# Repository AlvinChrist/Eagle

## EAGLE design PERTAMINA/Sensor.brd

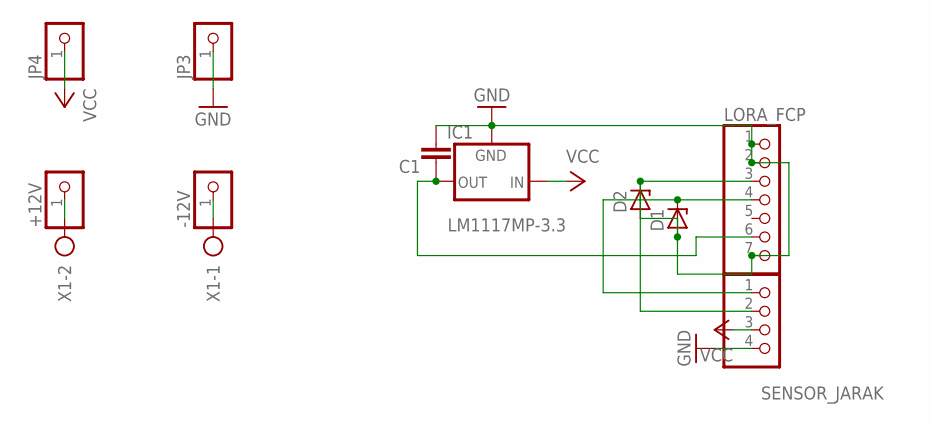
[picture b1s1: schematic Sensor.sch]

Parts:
+12V: PINHD-1X1; 1X01
-12V: PINHD-1X1; 1X01
C1: C-EU025-024X044; C025-024X044
D1, D2: ZENER-DIODEDO35Z10; DO35Z10
IC1: LM1117MP-3.3; SOT223
JP3, JP4: PINHD-1X1; 1X01
LORA_FCP: PINHD-1X7; 1X07
SENSOR_JARAK: PINHD-1X4; 1X04
X1: AK300/2

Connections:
3.3: C1.2, IC1.2 (OUT), IC1.4 (OUT), LORA_FCP.6
GND: C1.1, D1.A, D2.A, IC1.1 (GND), JP3.1, LORA_FCP.1, LORA_FCP.2, LORA_FCP.7, SENSOR_JARAK.4
GND12: -12V.1, X1.1
unnamed: +12V.1, X1.2
RX: D2.C, LORA_FCP.3, SENSOR_JARAK.2
TX: D1.C, LORA_FCP.4, SENSOR_JARAK.1
VCC: IC1.3 (IN), JP4.1, SENSOR_JARAK.3

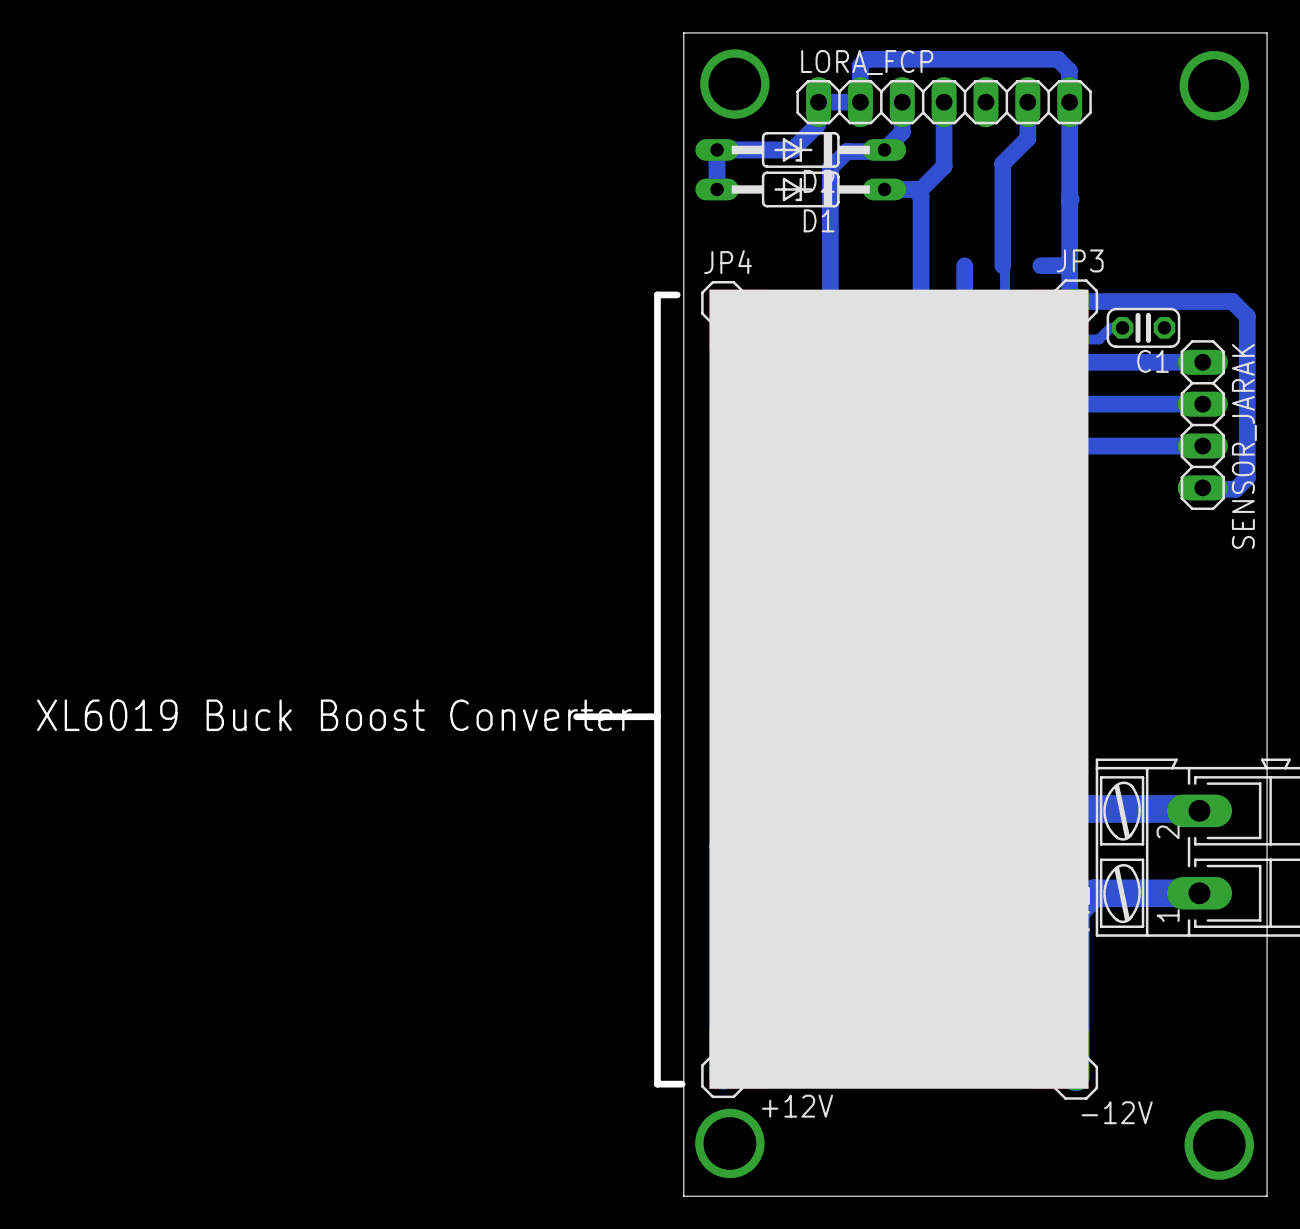
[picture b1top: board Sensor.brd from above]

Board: 2 copper layers, 35.4 x 70.6 mm, 11 parts (1 on the bottom side), 7 nets.

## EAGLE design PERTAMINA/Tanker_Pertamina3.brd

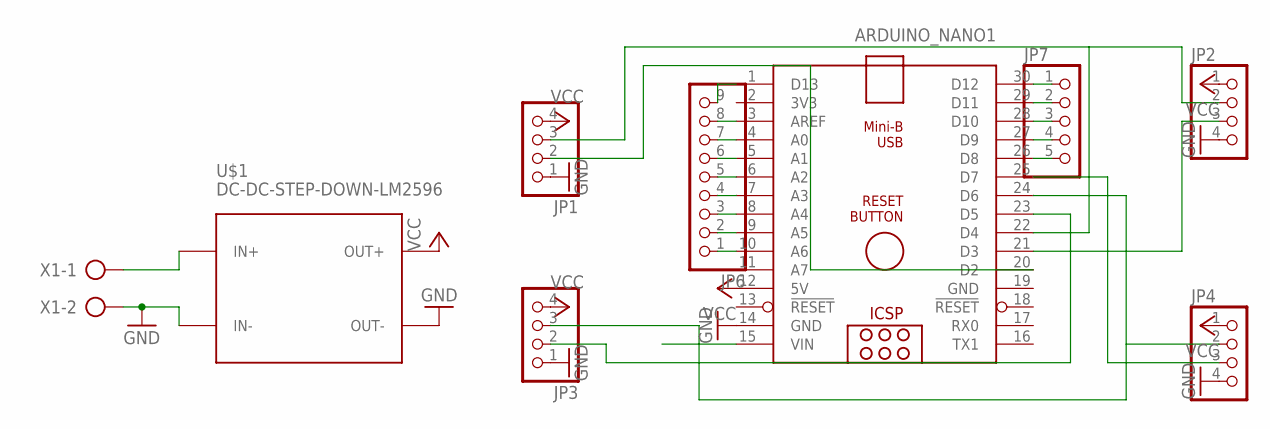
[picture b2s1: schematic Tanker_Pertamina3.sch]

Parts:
ARDUINO_NANO1: ARDUINO_NANO
JP1, JP2, JP3, JP4: PINHD-1X4; 1X04
JP6: PINHD-1X9; 1X09
JP7: PINHD-1X5; 1X05
U$1: DC-DC-STEP-DOWN-LM2596
X1: AK300/2

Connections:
7-12V: ARDUINO_NANO1.15 (VIN)
GND: ARDUINO_NANO1.14 (GND), ARDUINO_NANO1.19 (GND), JP1.1, JP2.4, JP3.1, JP4.4, U$1.IN-, U$1.OUT-, X1.2
unnamed: ARDUINO_NANO1.20 (D2), JP1.2
unnamed: ARDUINO_NANO1.10 (A6), JP6.1
unnamed: ARDUINO_NANO1.21 (D3), JP2.3
unnamed: ARDUINO_NANO1.23 (D5), JP3.2
unnamed: ARDUINO_NANO1.25 (D7), JP4.3
unnamed: ARDUINO_NANO1.9 (A5), JP6.2
unnamed: ARDUINO_NANO1.8 (A4), JP6.3
unnamed: ARDUINO_NANO1.7 (A3), JP6.4
unnamed: ARDUINO_NANO1.6 (A2), JP6.5
unnamed: ARDUINO_NANO1.5 (A1), JP6.6
unnamed: ARDUINO_NANO1.4 (A0), JP6.7
unnamed: ARDUINO_NANO1.3 (AREF), JP6.8
unnamed: ARDUINO_NANO1.1 (D13), JP6.9
unnamed: ARDUINO_NANO1.30 (D12), JP7.1
unnamed: ARDUINO_NANO1.29 (D11), JP7.2
unnamed: ARDUINO_NANO1.28 (D10), JP7.3
unnamed: ARDUINO_NANO1.27 (D9), JP7.4
unnamed: ARDUINO_NANO1.26 (D8), JP7.5
unnamed: U$1.IN+, X1.1
TRIGGER_BELAKANG: ARDUINO_NANO1.24 (D6), JP3.3, JP4.2
TRIG_DEPAN: ARDUINO_NANO1.22 (D4), JP1.3, JP2.2
VCC: ARDUINO_NANO1.12 (5V), JP1.4, JP2.1, JP3.4, JP4.1, U$1.OUT+

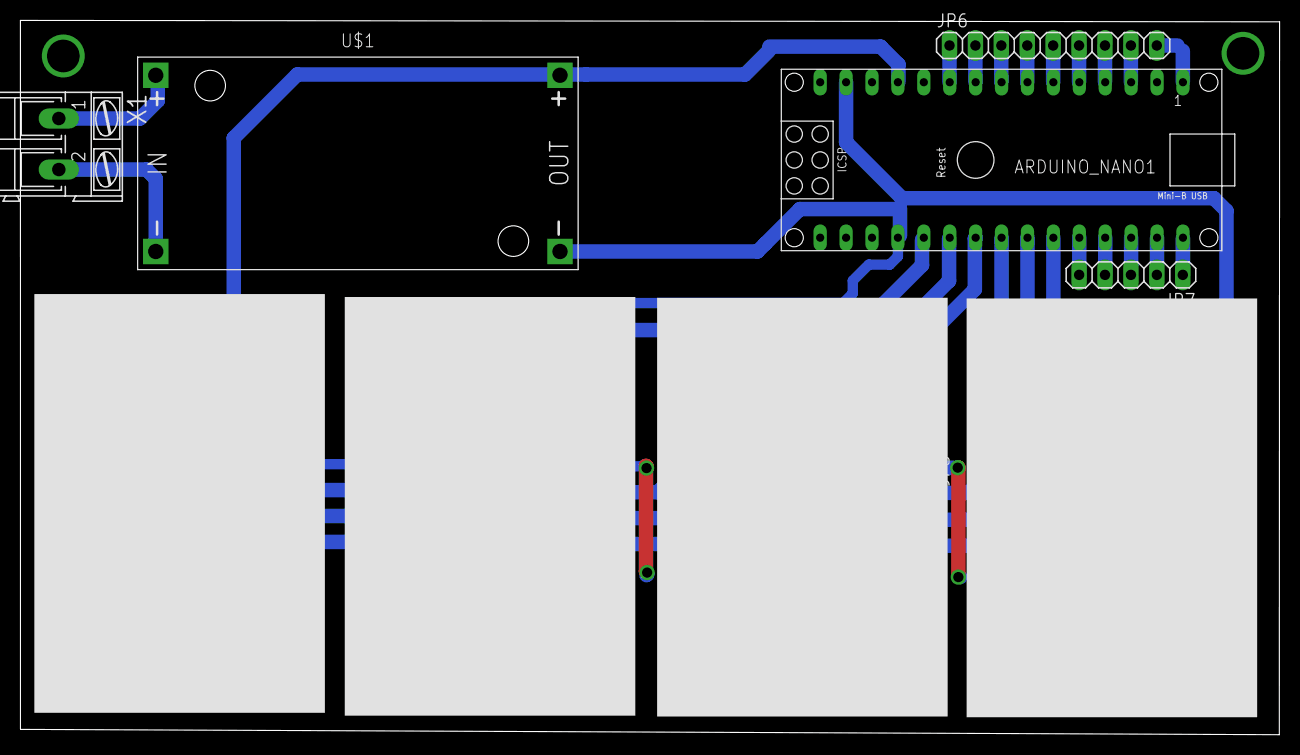
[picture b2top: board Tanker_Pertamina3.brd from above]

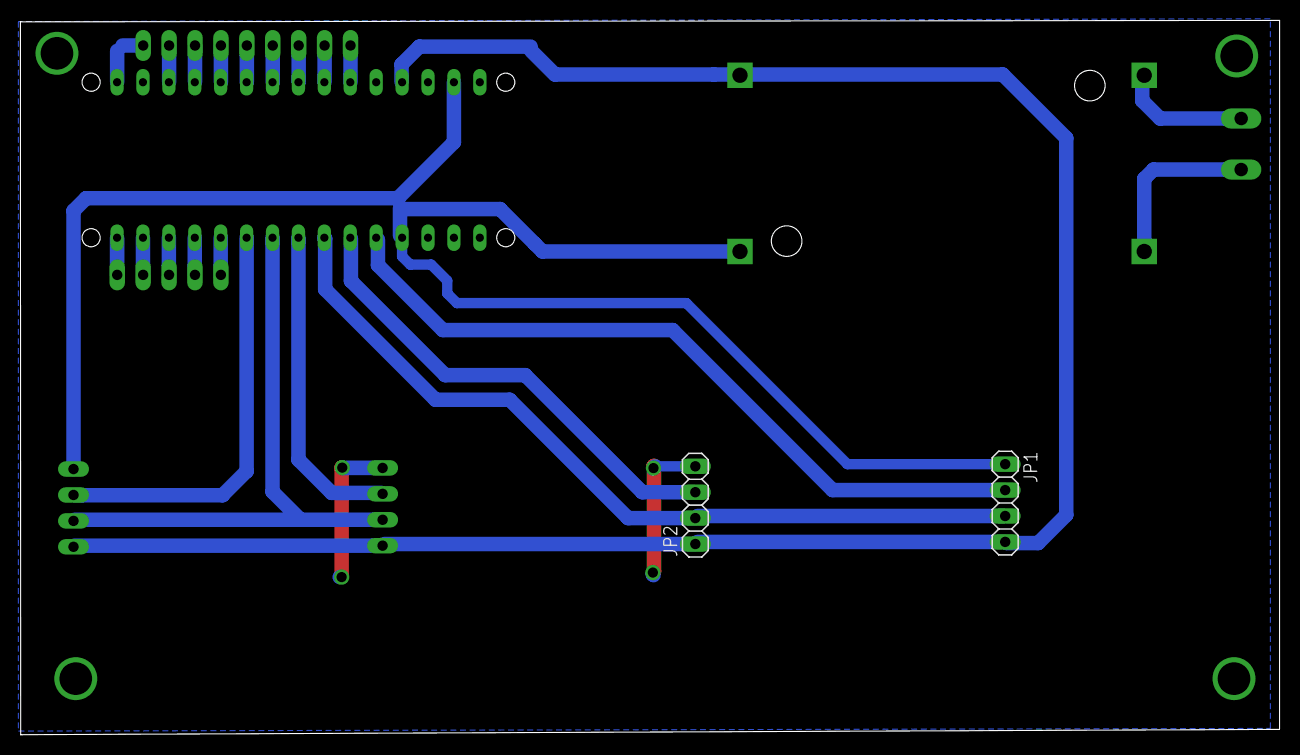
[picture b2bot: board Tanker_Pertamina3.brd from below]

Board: 2 copper layers, 123.4 x 70.0 mm, 9 parts (2 on the bottom side), 23 nets.

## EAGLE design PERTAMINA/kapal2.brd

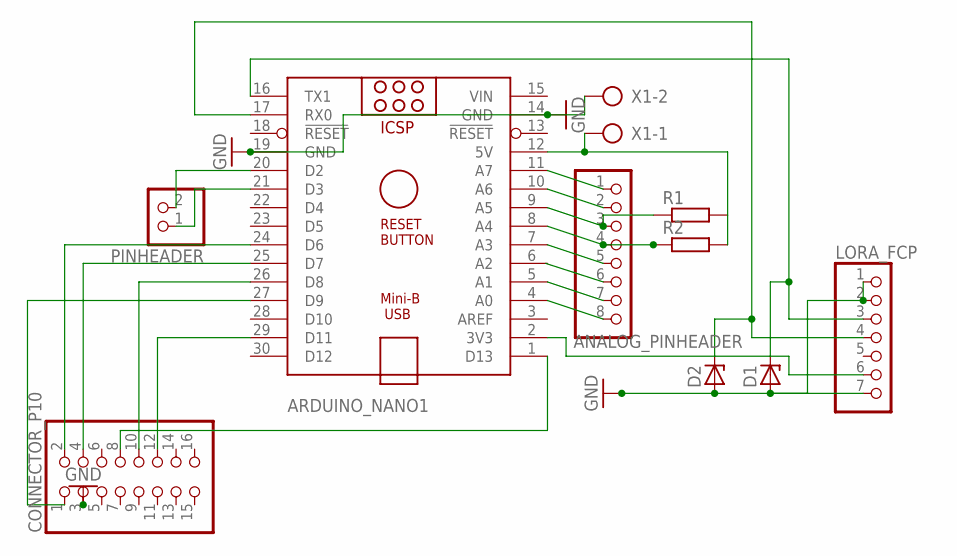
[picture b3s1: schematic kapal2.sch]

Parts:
ANALOG_PINHEADER: PINHD-1X8; 1X08
ARDUINO_NANO1: ARDUINO_NANO
CONNECTOR_P10: PINHD-2X8; 2X08
D1, D2: ZENER-DIODEDO35Z10; DO35Z10
LORA_FCP: PINHD-1X7; 1X07
PINHEADER: PINHD-1X2; 1X02
R1, R2: R-EU_0204/7; 0204/7
X1: AK300/2

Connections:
D7: ARDUINO_NANO1.25 (D7), CONNECTOR_P10.4
D13: ARDUINO_NANO1.1 (D13), CONNECTOR_P10.8
GND: ARDUINO_NANO1.14 (GND), ARDUINO_NANO1.19 (GND), CONNECTOR_P10.3, D1.A, D2.A, LORA_FCP.1, LORA_FCP.2, LORA_FCP.7, X1.2
unnamed: ARDUINO_NANO1.27 (D9), CONNECTOR_P10.1
unnamed: ARDUINO_NANO1.16 (TX1), D1.C, LORA_FCP.3
unnamed: ARDUINO_NANO1.24 (D6), CONNECTOR_P10.2
unnamed: ARDUINO_NANO1.26 (D8), CONNECTOR_P10.10
unnamed: ARDUINO_NANO1.29 (D11), CONNECTOR_P10.12
unnamed: ANALOG_PINHEADER.3, ARDUINO_NANO1.9 (A5), R1.1
unnamed: ARDUINO_NANO1.12 (5V), R1.2, R2.2, X1.1
unnamed: ARDUINO_NANO1.17 (RX0), D2.C, LORA_FCP.4
unnamed: ARDUINO_NANO1.20 (D2), PINHEADER.2
unnamed: ARDUINO_NANO1.2 (3V3), LORA_FCP.6
unnamed: ARDUINO_NANO1.21 (D3), PINHEADER.1
unnamed: ANALOG_PINHEADER.1, ARDUINO_NANO1.11 (A7)
unnamed: ANALOG_PINHEADER.2, ARDUINO_NANO1.10 (A6)
unnamed: ANALOG_PINHEADER.4, ARDUINO_NANO1.8 (A4), R2.1
unnamed: ANALOG_PINHEADER.5, ARDUINO_NANO1.7 (A3)
unnamed: ANALOG_PINHEADER.7, ARDUINO_NANO1.5 (A1)
unnamed: ANALOG_PINHEADER.8, ARDUINO_NANO1.4 (A0)
VIN: ARDUINO_NANO1.15 (VIN)

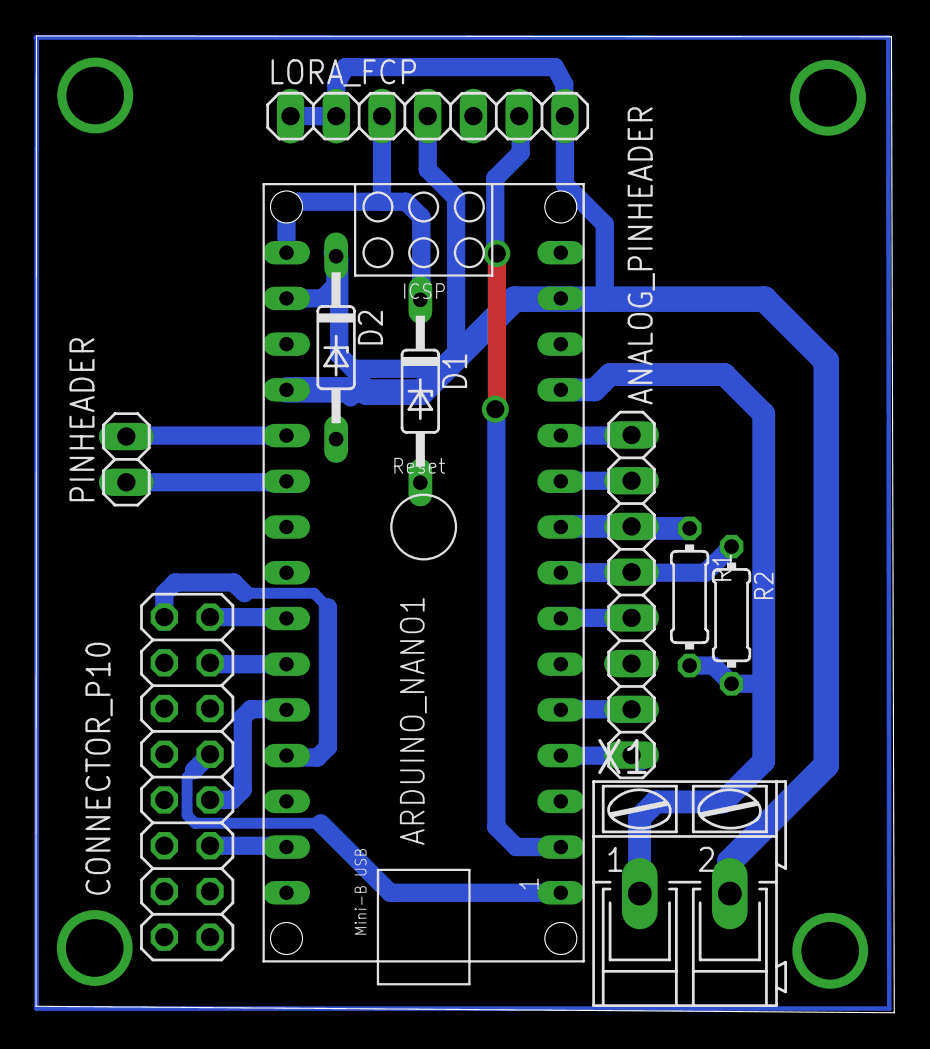
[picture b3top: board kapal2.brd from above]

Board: 2 copper layers, 47.7 x 54.3 mm, 10 parts (0 on the bottom side), 20 nets.

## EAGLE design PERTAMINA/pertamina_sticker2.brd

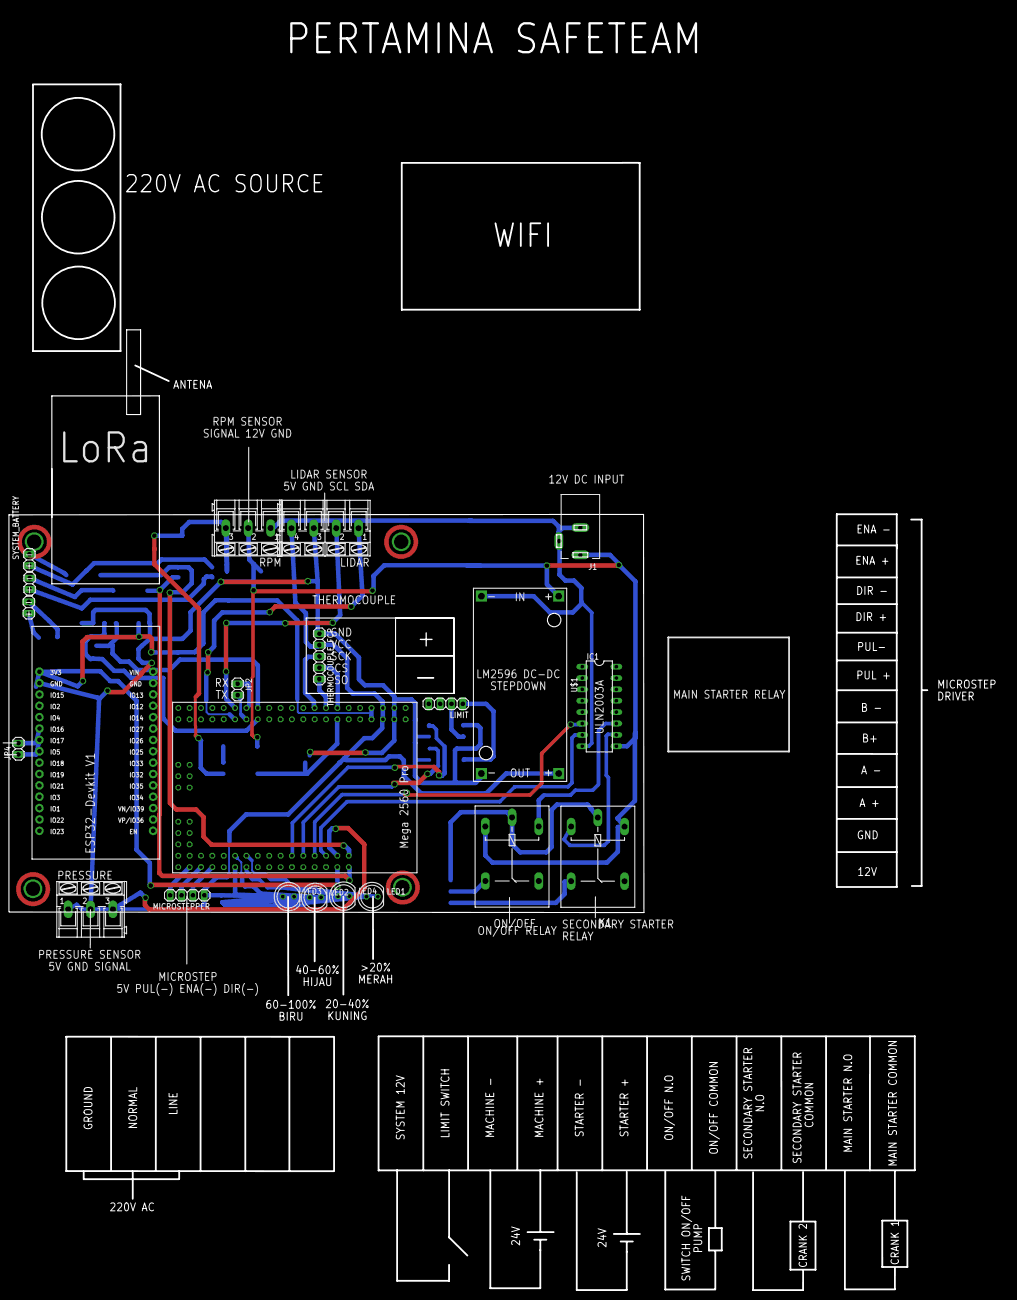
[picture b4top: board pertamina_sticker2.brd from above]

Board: 2 copper layers, 205.2 x 269.4 mm, 22 parts (0 on the bottom side), 26 nets.

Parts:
IC1: ULN2003AN; DIL16
J1: DCJ0202
JP2, JP4: 1X02
K1: G5L; G5LE
LED1, LED2, LED3, LED4: LED5MM
LIDAR: AK300/4
LIMIT: 1X04
MACHINE_BATTERY_12V: 1X02
MICROSTEPPER: 1X04
ON/OFF: G5L; G5LE
PRESSURE: AK300/3
RPM: AK300/3
STARTER_BATTERY1: 1X02
SYSTEM_BATTERY: 1X02
THERMOCOUPLE_FCP: 1X05
U$1: DC-DC-STEP-DOWN-LM2596
U$2: ESP32-DEVKITV1
U$3: MEGAPROMINI

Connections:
3.3V: U$2.3V3, U$3.P$7, U$3.P$8
5V_ARDU: LED1.A, LED2.A, LED3.A, LED4.A, LIDAR.4, MICROSTEPPER.1, PRESSURE.1, THERMOCOUPLE_FCP.2, U$1.OUT+, U$3.P$5, U$3.P$6
GND: IC1.9, J1.1, K1.2, LIDAR.3, ON/OFF.1, PRESSURE.2, RPM.2, THERMOCOUPLE_FCP.1, U$1.IN+, U$1.OUT-, U$2.GND@2, U$3.P$3, U$3.P$4
unnamed: JP2.1, U$3.P$30
unnamed: JP2.2, U$3.P$29
unnamed: IC1.10, K1.1
unnamed: THERMOCOUPLE_FCP.5, U$3.P$16
unnamed: THERMOCOUPLE_FCP.4, U$3.P$14
unnamed: THERMOCOUPLE_FCP.3, U$3.P$18
unnamed: IC1.8, J1.2, J1.3, RPM.1, U$1.IN-
unnamed: JP4.1, U$2.D17
unnamed: JP4.2, U$2.D16
unnamed: IC1.7, U$3.P$48
unnamed: IC1.6, U$3.P$50
unnamed: MICROSTEPPER.4, U$3.P$71
unnamed: MICROSTEPPER.2, U$3.P$67
unnamed: MICROSTEPPER.3, U$3.P$69
unnamed: PRESSURE.3, U$3.P$46
unnamed: IC1.11, ON/OFF.2
unnamed: LED2.K, U$3.P$64
unnamed: LED3.K, U$3.P$63
unnamed: LED1.K, U$3.P$62
unnamed: LED4.K, U$3.P$61
unnamed: K1.P, ON/OFF.P
SCL: LIDAR.2, U$3.P$32
SDA: LIDAR.1, U$3.P$31

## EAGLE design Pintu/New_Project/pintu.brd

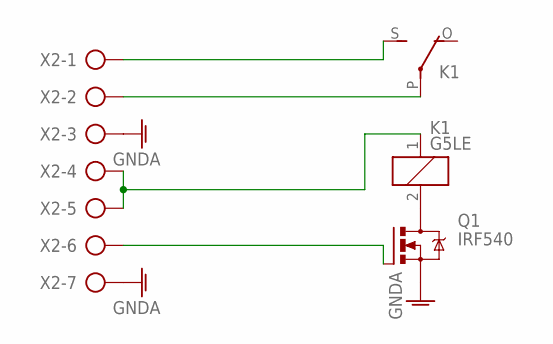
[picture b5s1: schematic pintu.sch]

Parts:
K1: G5LE
Q1: IRF540; TO220BV
X2: AK300/7

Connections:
12V: K1.1, X2.4, X2.5
GNDA: Q1.S, X2.3, X2.7
L2: K1.P, X2.2
unnamed: K1.2, Q1.D
unnamed: Q1.G, X2.6
unnamed: K1.S, X2.1

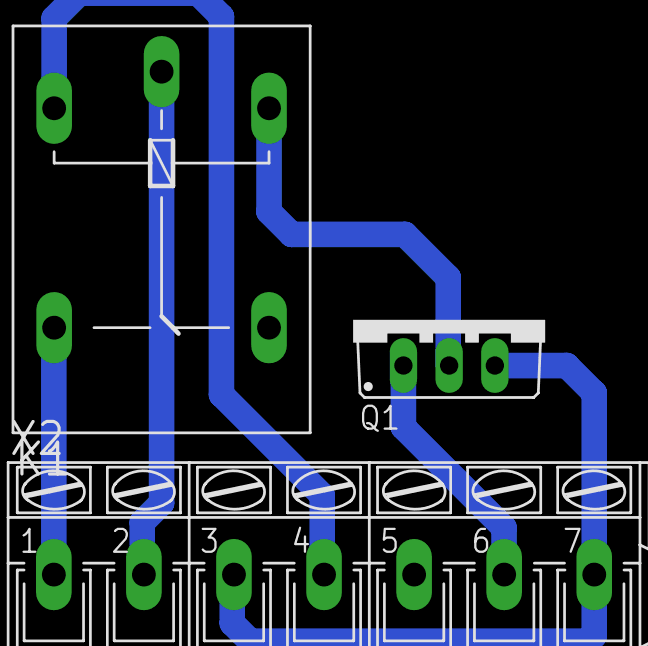
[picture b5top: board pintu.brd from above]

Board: 2 copper layers, 3 parts (0 on the bottom side), 6 nets.

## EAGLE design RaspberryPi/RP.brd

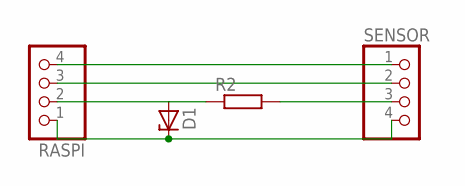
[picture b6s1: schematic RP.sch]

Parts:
D1: ZENER-DIODEDO35Z10; DO35Z10
R2: R-EU_0204/7; 0204/7
RASPI: PINHD-1X4; 1X04
SENSOR: PINHD-1X4; 1X04

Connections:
5V: RASPI.4, SENSOR.1
ECHO: D1.A, R2.1, RASPI.2
unnamed: D1.C, RASPI.1, SENSOR.4
unnamed: R2.2, SENSOR.3
TRIG: RASPI.3, SENSOR.2

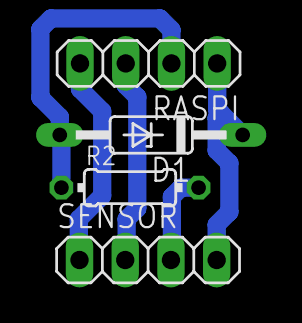
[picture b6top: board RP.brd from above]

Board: 2 copper layers, 4 parts (0 on the bottom side), 5 nets.

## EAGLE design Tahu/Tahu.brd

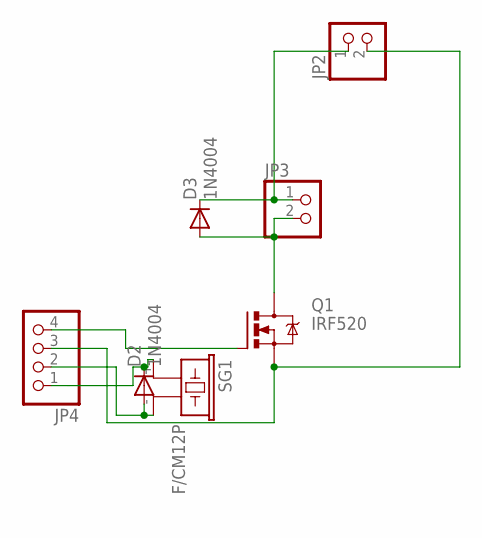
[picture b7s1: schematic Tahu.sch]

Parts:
D2, D3: 1N4004; DO41-10
JP2, JP3: PINHD-1X2; 1X02
JP4: PINHD-1X4; 1X04
Q1: IRF520; TO220BV
SG1: F/CM12P

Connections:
5V: D2.C, JP4.1, SG1.+ (1)
24V: D3.C, JP2.1, JP3.1
GND: JP2.2, JP4.3, Q1.S
unnamed: D2.A, JP4.2, SG1.- (2)
unnamed: JP4.4, Q1.G
unnamed: D3.A, JP3.2, Q1.D

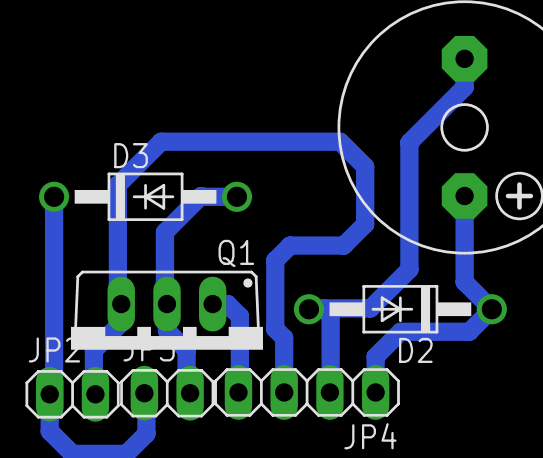
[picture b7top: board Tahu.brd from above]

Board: 2 copper layers, 7 parts (0 on the bottom side), 6 nets.

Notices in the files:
parts and their libraries:
lm1117: (c) 2014 Samuel Lourenço
diy-modules: Released under the Creative Commons Attribution 4.0 International License: http://creativecommons.org/licenses/by/4.0
